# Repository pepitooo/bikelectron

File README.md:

# BikElectron
Personnal project to illumate rim on a bike during night, "Tron" effect

## Why this project ?
To be simple, I was not satisfy with the common lightning system. I saw on kickstarter some project with led around the rim, but it had too much constraints and it was so visible during day. Then the idea : using "glow in the dark" stickers.

## First prototype
The [first prototype](https://github.com/pepitooo/OpenSCAD_leds_support) was not too bad, using a flashlight from DX.com or AliExpress and some glow in the dark tape.

I was not so happy with the size of each led support and fix system was not good at all.

# Project parts

## Electronic
It's so basic, 2 times a resitor and a UV/blacklight led in parallel.

## PCB

## Battery pack
I took a battery pack used to charge phone, it's cheap, and powerfull enough.
I used a USB cable for wiring all modules togeter.

## Case 3D printed

## Stickers
I used glow in the dark vinyl warp and lazer cut it. If you are precise enough cisor can do the job.

## All elements together

# Final product

You need to sold in serial 2 led module for each wheel using the USB cable.
On the picture of the final product the front wheel is more blue than rear, it's because I bought some blue glow in the dark tape. 

I used the stickers lazer cut for the front wheel, and for the rear wheel it's from the [first prototype](https://github.com/pepitooo/OpenSCAD_leds_support) where I used 10mm tape, and cut in a lot of small piece to cover all the rim.

If you want to do the same, take a good quality glow in the dark viny to have a shiny light. The chinese seller use hour of light after illumination as "quality" take one with at least 12 hours.

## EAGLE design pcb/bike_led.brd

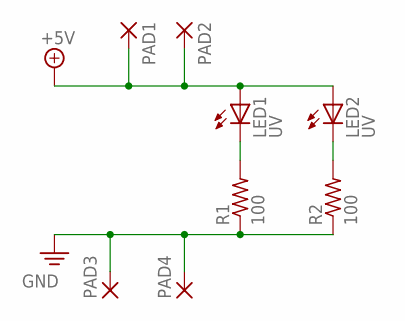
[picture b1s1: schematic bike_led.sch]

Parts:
LED1, LED2: UV; 1206
PAD1, PAD2, PAD3, PAD4: SMD5; SMD2,54-5,08
R1, R2: 100; R1206

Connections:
+5V: LED1.A, LED2.A, PAD1.1, PAD2.1
GND: PAD3.1, PAD4.1, R1.1, R2.1
unnamed: LED2.C, R2.2
unnamed: LED1.C, R1.2

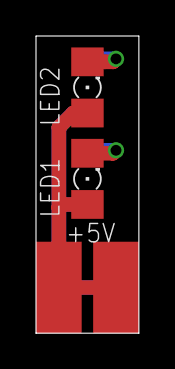
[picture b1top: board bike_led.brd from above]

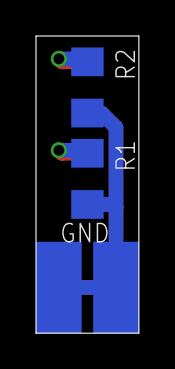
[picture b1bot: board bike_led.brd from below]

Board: 2 copper layers, 5.7 x 16.5 mm, 8 parts (4 on the bottom side), 4 nets.

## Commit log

2015-08-06 folder structure
2015-08-06 group all part of the project in a repo
2015-08-06 sticker cad for being cut by a lazer at FabLab Zurich
2015-08-06 New picture added with all parts, pcb, 3d printed case, cutted stickers, battery pack
2015-08-07 change led windows side using a boolean
2015-08-11 enlarge sticker width to 11mm
2015-08-11 add a new layer with 4 points to position correctly the paper
2015-08-16 Picture of the final product in the dark with light on
2015-08-16 Schematic of PCB
2015-08-16 Stickers screenshot
2015-08-16 A bit of doc is not bad
